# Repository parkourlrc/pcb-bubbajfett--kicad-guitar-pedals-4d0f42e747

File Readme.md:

# Current guitar pedal projects 

Current count of pedals in this repo is something like 40.    Not doing too many more, though I have a FV-1 and a Daisy seed one I'm working on longer term, as well as clearing out the box of shame.  I have been stymied on a number of recent pedal builds testing out of box due to the rig I was using having some kind of bad wires, causing huge amounts of hum.    I reworked the testing rig and have now verified about 6 or 7 more in last week.

Anyway, the requirements here are KICAD 7 or later.     Each subdir has a gerbers directory, which has the final set of gerbers used.    

The latest change is to add a PDF in the root of each pedal directory, which has the readme, the schematic as an image, and the front and back layout of the PCB (F.Cu+F.Silkscreen, B.Cu+F.Silkscreen). Also a BOM of the parts is included.    This was all done scripted using kicad-cli  in a VM (Fedora 44, Kicad 10 !!!) as the Kicad 7 versions of this did not work very well.   I will add pics of the real tested boards as an addendum to these.    This change was a result of some feedback I recieved about the lack of clarity of what is in this repo.

These pedals have been a learning exercise for me in KiCad. Any guitar pedal PCB published here has been built and tested. In some cases, more than two versions of boards have been created.   The worst case was 5 versions.

The main idea for doing my own PCB is to allow me to change the footprints and merge and/or hack pedal schematics to come up with new ideas.
The other reason is I am redoing my pedalboard to convert from side-jacks/veroboard layout to  top-jacks/pcbs.   I have gotten to dislike veroboard layouts.

I am an amateur in this.   Also this has been a huge learning exercise.    I've tried to be consistent with some design decisions.

*   back of board mounted POTs.   Tried using both 16mm and 9mm pots (RK97?)
*   common format pinheader so to be able to use 4pin dupont connector or JST connector when building.   The topjacks pcb broke this "common format (9v, Out, In, Gnd --- from left to right)",
in that it was initially intended that the PCB be oriented closest to the the 125B shell bottom, but that made assembly more difficult.   I ordered panels of it from JLPCB, and so I;m just wiring them
backwards.
*   power on the top jack connector, with diode protection there.
*   led on the stomp switch
*   125B form factor.    Top jacks in a 1590B is really hard unless the power connector is modified or moved somewhere else.

One thing I have learned is that the text size on some of these boards is below
the JLPCB minimum recommended size; the text looks fine in osh-park boards.

Several of the build docs have pictures of the final builds.    Tonemachine is the latest...

Putting these pedal layouts out there for any interested party.   Do what you want with them. 

Here are the current repo contents.   These have all been tested outside the box,
and multiple have been successfully boxed.  12  have been boxed and are 
now on the pedalboard. 

| PEDAL | BUILD DOC | Verified|
| ----  | -------   | ------- |
| Delay/deep_blue_delay | [deep-blue-delay](./Delay/deep_blue_delay/deep_blue_delay.pdf) | Y |
| Util/stomp-chargepump |  [stomp-chargepump](./Util/stomp-chargepump/stomp-chargepump.pdf) | Y |
| Util/stomp-3pdt | [stomp-3pdt](./Util/stomp-3pdt/stomp-3pdt.pdf) | Y | 
| Util/top-jacks | [top-jacks](./Util/top-jacks/top-jacks.pdf) | Y |
| Distortion/900fuzz | [900fuzz](./Distortion/900fuzz/900fuzz.pdf) | Y |
| Distortion/acapulcogold | [acapulcogold](./Distortion/acapulcogold/acapulcogold.pdf) | Y |
| Distortion/bigmuff | [bigmuff](./Distortion/bigmuff/bigmuff.pdf) | Y | 
| Distortion/bigmuff/bmp-ramshead  | --- | Y |
| Distortion/blackdarling | --- | Y |
| Distortion/brutalistjr | [brutalist jr](./Distortion/brutalistjr/brutalistjr.pdf) | Y |
| Distortion/bmp2 | [BMP2](./Distortion/bmp2/bmp2.pdf) | Y |
| Distortion/ejfuzzface | [ejfuzzface](./Distortion/ejfuzzface/ejfuzzface.pdf) | Y |
| Distortion/fortinfuzz | [fortinfuzz](./Distortion/fortinfuzz/fortinfuzz.pdf) | Y |
| Distortion/fuzzface | [fuzzface](./Distortion/fuzzface/fuzzface.pdf) | Y |
| Distortion/fy2 | [Shin-ey fy2](./Distortion/fy2/fy2.pdf) | Y  |
| Distortion/lizardq | [lizardq](./Distortion/lizardq/lizardq.pdf) | Y | 
| Distortion/percolator | [percolator](./Distortion/percolator/percolator.pdf) | Y |
| Distortion/tonemachine | [tonemachine](./Distortion/tonemachine/tonemachine.pdf) | Y |
| Distortion/redllama | [redllama](./Distortion/redllama/redllama.pdf) | Y |
| Distortion/whitefuzz | [whitefuzz](./Distortion/whitefuzz/whitefuzz.pdf) | Y |
| Compressor/bearhug | [bearhug](./Compressor/bearhug/bearhug.pdf) | Y | 
| Compressor/engineers_thumb | [engineers_thumb](./Compressor/engineers_thumb/engineers_thumb.pdf) | Y |
| Compressor/dynacomp | ---  | Maybe? |
| Compressor/dynacomp-lm13700  | --- | N |
| Chorus/littleangel | [littleangel](./Chorus/littleangel/littleangel.pdf) | Y |
| Envelope/mutron | [mutron-v](./Envelope/mutron/mutron.pdf) | Y |
| Overdrive/badmonkey | [badmonkey](./Overdrive/badmonkey/badmonkey.pdf) | Y |
| Overdrive/bsiab |  [bsiab](./Overdrive/bsiab/bsiab.pdf) | Y |
| Overdrive/beod |  [beod](./Overdrive/beod/beod.pdf) | Y |
| Overdrive/drboogie | ... | Y |
| Overdrive/ecstacy | [ecstacy](./Overdrive/ecstacy/ecstacy.pdf) | Y | 
| Overdrive/fatdrive | [fatdrive](./Overdrive/fatdrive/fatdrive.pdf)| Y |
| Overdrive/KoT | [KoT](./Overdrive/KoT/KoT.pdf) | Y | 
| Overdrive/ocd | [ocd](./Overdrive/ocd/ocd.pdf) | Y |
| Overdrive/revv-g4 | [revv-g4](./Overdrive/revv-g4/revv-g4.pdf) | Y |
| Overdrive/SFTii | [sftii](./Overdrive/SFTii/SFTii.pdf) | Y | 
| Overdrive/timmy  | [timmy](./Overdrive/timmy/timmy.pdf) | Y |
| Overdrive/triple_wreck | [triple_wreck](./Overdrive/triple_wreck/triple_wreck.pdf) | Y | 
| Overdrive/tweed57 | [tweed57](./Overdrive/tweed57/tweed57.pdf)|Y|
| Overdrive/umble | [umble](./Overdrive/umble/umble.pdf) | Y |
| Equalizer/eq | [eq](./Equalizer/eq/eq.pdf) | Y | 

PCB builds in progress are

*   Barbershop (redo)
*   paisley
*   plexidrive
*   Klon

*   phase45
*   g2
*   bluesdriver
*   katzenkonig
*   sabbracadabra
*   tubescreamer

And 4 are stuck in the box of shame 
*   zombiechorus (9 months non-working...)
*   causalty4 phaser  (ugggh ... so close)
*   box of metal      
*   kraken

All the above subprojects have a gerbers/ subdir with the last gerber file I generated. Using OshPark for pcb generation.    They were done with Kicad 7.
Most were done with manual placement of the elements on the PCB, and then using freerouting to autoroute the traces.

License is the general Creative Commons.     Have fun!

All registered trademarks are owned by their respective owners.

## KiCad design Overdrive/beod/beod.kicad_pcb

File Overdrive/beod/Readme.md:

#  beod  overdrive

This is a clone of the BEOD overdrive pedal from Friedman
Amplification, which is based, I think, on the Friedman BE-100.  The
schematic that was used for this seems similar to the pcbguitarmania
one, but I think I downloaded it from freestompboxes.

This was thought to be broken and I was debugging for several weeks
until I realized the kit I was using to test the bare PCB had a broken
wire.

This thing is $##@$@# loud.   This is a definite will-box pedal.

This pedal is verified.

All trademarks belong to their respective owners.

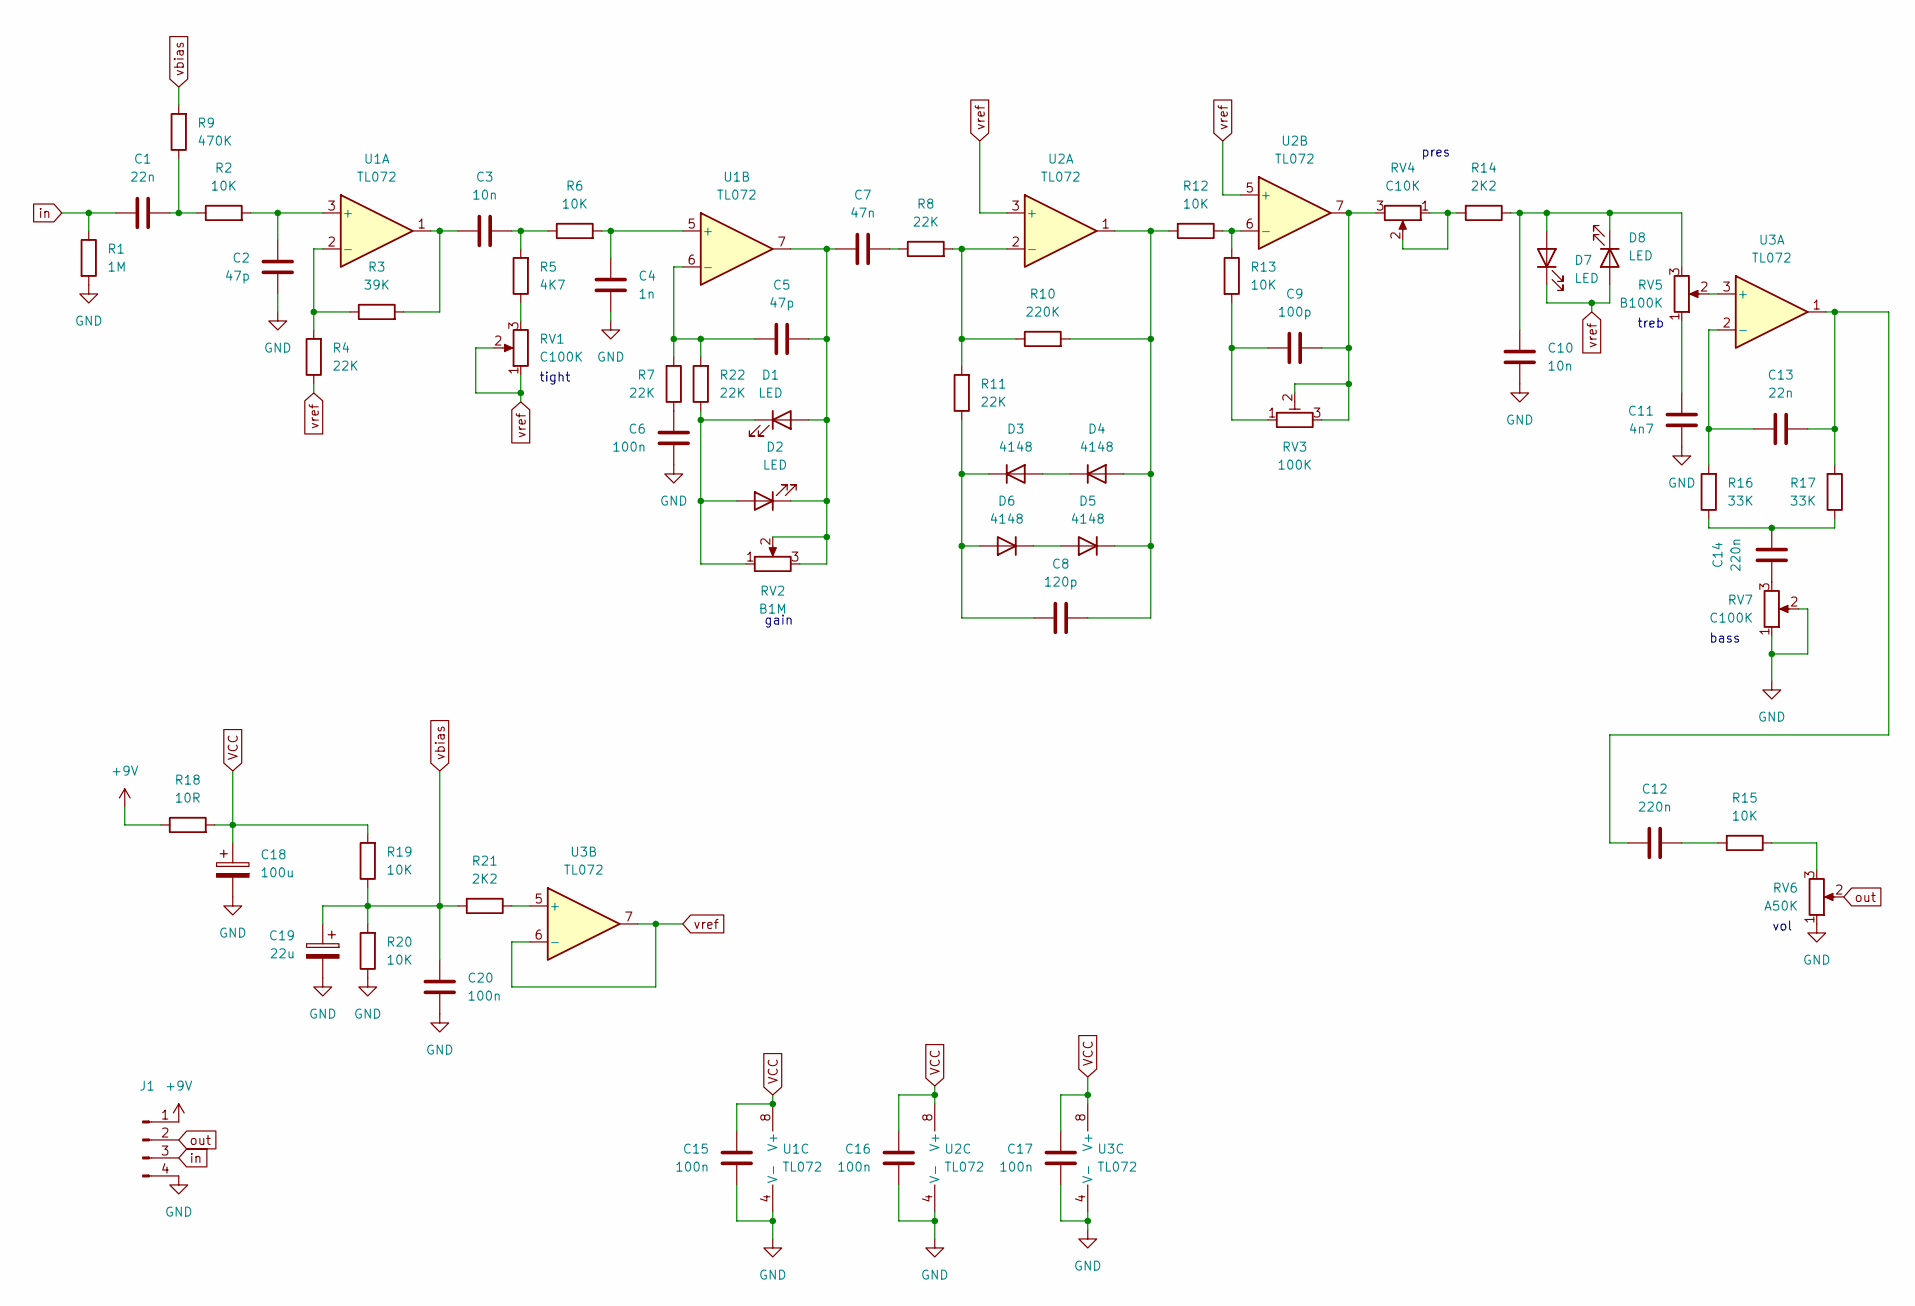
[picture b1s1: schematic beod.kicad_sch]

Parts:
C1, C13: 22n; C_Rect_L7.0mm_W2.0mm_P5.00mm
C2, C5: 47p; C_Rect_L7.0mm_W2.0mm_P5.00mm
C3, C10: 10n; C_Rect_L7.0mm_W2.0mm_P5.00mm
C4: 1n; C_Rect_L7.0mm_W2.0mm_P5.00mm
C6, C15, C16, C17, C20: 100n; C_Rect_L7.0mm_W2.5mm_P5.00mm
C7: 47n; C_Rect_L7.0mm_W2.0mm_P5.00mm
C8: 120p; C_Rect_L7.0mm_W2.0mm_P5.00mm
C9: 100p; C_Rect_L7.0mm_W2.0mm_P5.00mm
C11: 4n7; C_Rect_L7.0mm_W2.0mm_P5.00mm
C12, C14: 220n; C_Rect_L7.0mm_W2.0mm_P5.00mm
C18: 100u; CP_Radial_D6.3mm_P2.50mm
C19: 22u; CP_Radial_D5.0mm_P2.00mm
D1, D2, D7, D8: LED; LED_D3.0mm
D3, D4, D5, D6: 4148; D_DO-34_SOD68_P7.62mm_Horizontal
J1: Conn_01x04_Pin; PinSocket_1x04_P2.54mm_Vertical
R1: 1M; R_Axial_DIN0207_L6.3mm_D2.5mm_P10.16mm_Horizontal
R2, R6, R12, R13, R15, R19, R20: 10K; R_Axial_DIN0207_L6.3mm_D2.5mm_P10.16mm_Horizontal
R3: 39K; R_Axial_DIN0207_L6.3mm_D2.5mm_P10.16mm_Horizontal
R4, R7, R8, R11, R22: 22K; R_Axial_DIN0207_L6.3mm_D2.5mm_P10.16mm_Horizontal
R5: 4K7; R_Axial_DIN0207_L6.3mm_D2.5mm_P10.16mm_Horizontal
R9: 470K; R_Axial_DIN0207_L6.3mm_D2.5mm_P10.16mm_Horizontal
R10: 220K; R_Axial_DIN0207_L6.3mm_D2.5mm_P10.16mm_Horizontal
R14, R21: 2K2; R_Axial_DIN0207_L6.3mm_D2.5mm_P10.16mm_Horizontal
R16, R17: 33K; R_Axial_DIN0207_L6.3mm_D2.5mm_P10.16mm_Horizontal
R18: 10R; R_Axial_DIN0207_L6.3mm_D2.5mm_P10.16mm_Horizontal
RV1, RV7: C100K; Pot_Underside
RV2: B1M; Pot_Underside
RV3: 100K; Potentiometer_Runtron_RM-065_Vertical
RV4: C10K; Pot_Underside
RV5: B100K; Pot_Underside
RV6: A50K; Pot_Underside
U1, U2, U3: TL072; DIP-8_W7.62mm

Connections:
+9V: J1.1, R18.1
GND: C2.1, C4.2, C6.2, C10.2, C11.2, C15.2, C16.2, C17.2, C18.2, C19.2, C20.2, J1.4, R1.2, R20.1, RV6.1, RV7.1, RV7.2, U1.4 (V-), U2.4 (V-), U3.4 (V-)
unnamed: C1.2, R2.1, R9.1
unnamed: C3.1, R5.2, R6.1
unnamed: C3.2, R3.2, U1.1
unnamed: C6.1, R7.1
unnamed: C7.1, R8.1
unnamed: C9.1, R13.2, RV3.1
unnamed: C9.2, RV3.2, RV3.3, RV4.3, U2.7
unnamed: C11.1, RV5.1
unnamed: C12.1, C13.2, R17.2, U3.1
unnamed: C12.2, R15.2
unnamed: C14.1, RV7.3
unnamed: C14.2, R16.1, R17.1
unnamed: C5.2, C7.2, D1.2 (A), D2.1 (K), RV2.2, RV2.3, U1.7
unnamed: D1.1 (K), D2.2 (A), R22.1, RV2.1
unnamed: D3.2 (A), D4.1 (K)
unnamed: C8.1, D3.1 (K), D6.2 (A), R11.1
unnamed: C8.2, D4.2 (A), D5.1 (K), R10.2, R12.2, U2.1
unnamed: D5.2 (A), D6.1 (K)
unnamed: C10.1, D7.2 (A), D8.1 (K), R14.1, RV5.3
unnamed: R5.1, RV1.3
unnamed: R14.2, RV4.1, RV4.2
unnamed: R15.1, RV6.3
unnamed: C2.2, R2.2, U1.3 (+)
unnamed: R3.1, R4.2, U1.2 (-)
unnamed: C4.1, R6.2, U1.5 (+)
unnamed: C5.1, R7.2, R22.2, U1.6 (-)
unnamed: R8.2, R10.1, R11.2, U2.2 (-)
unnamed: R12.1, R13.1, U2.6 (-)
unnamed: RV5.2, U3.3 (+)
unnamed: C13.1, R16.2, U3.2 (-)
unnamed: R21.1, U3.5 (+)
VCC: C15.1, C16.1, C17.1, C18.1, R18.2, R19.2, U1.8 (V+), U2.8 (V+), U3.8 (V+)
in: C1.1, J1.3, R1.1
out: J1.2, RV6.2
vbias: C19.1, C20.1, R9.2, R19.1, R20.2, R21.2
vref: D7.1 (K), D8.2 (A), R4.1, RV1.1, RV1.2, U2.3 (+), U2.5 (+), U3.6 (-), U3.7

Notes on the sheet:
bass
vol
pres
gain
tight
treb

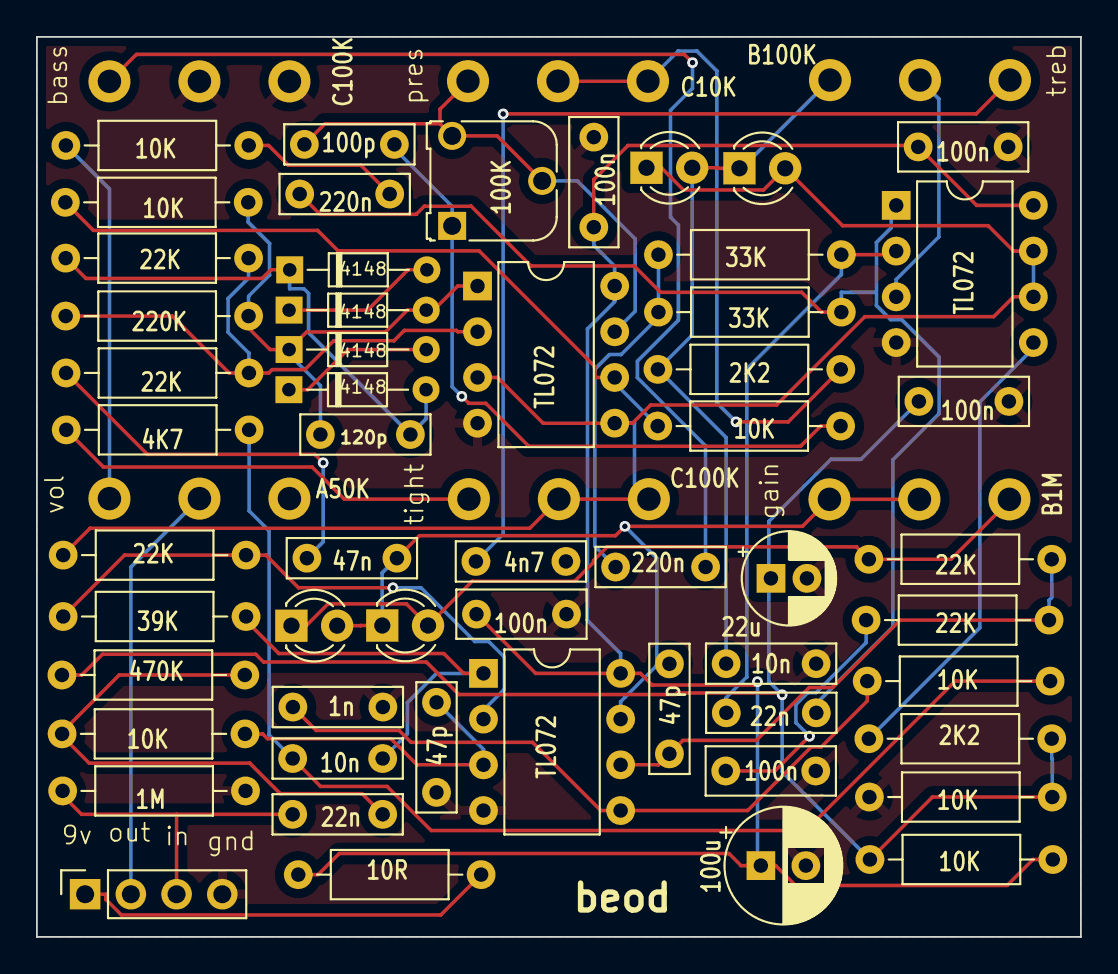
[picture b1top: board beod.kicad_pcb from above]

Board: 2 copper layers, 58.0 x 50.0 mm, 61 parts (0 on the bottom side), 38 nets.
